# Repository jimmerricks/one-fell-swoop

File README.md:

# Swoop

A WIP fork of [David Barr's Sweep](https://github.com/davidphilipbarr/Sweep), which is itself based on the fabulous [Ferris by Pierre Chevalier](https://github.com/pierrechevalier83/ferris).

<span>

</span>

## Swoop MX / Howarya 🦞

| Front | Back |
| :---: | :---: |
|  |  |

### Features
⭕ Cherry MX style switches  
⭕ Hotswap support  
⭕ Per-key RGB LEDs (mini-e)  
⭕ Up to 2 encoders  
⭕ Oled screens  
⭕ Power switch for battery management  
⭕ Bluetooth support w/ nice!nano  
⭕ Plate style case with mcu cover

### Components list

To build and use a Swoop MX you will need:

* 1× PCB Kit
* 2× promicro compatible boards or 2 nice!nanos.
* 34-36× Cherry MX style switches
* 34-36× Kailh hotswap sockets
* 34-36× SK6812 Mini-E RGB SMD Leds (optional; not recommended for wireless)
* 34-36× keycaps
* 36× diodes (Surface-mount or Through-hole)
* 2× Rotary encoders & knobs (optional; ALPS EC11)
* 2× OLED LCD Display 128x32 SSD1306 (optional)
* 2× reset switches (optional; B3U-1000P(M))
* Some little rubber feet/bumpers
* 2× power switches (wireless only; MSK 12C02)
* 2× lipo batteries (wireless only; 301230 or 301228)
* 1× TRRS (not TRS!) cable (wired only)
* 2× TRRS Jack [PJ-320A] (wired only)
* 1× USB Cable (depends on your micro-controller choice)  

**For the case:**

* 32× M2 Screws (3mm thread length)  
* 10× M2 Standoff for the plates (7mm)
* 6× M2 Standoff for the controller cover (8mm)

### Price Estimate (5 keyboards)
* PCB - 10.13 USD
* Carbon fiber plate 1.6mm (base, switch, cover) - 37.09 USD
* Crylic plate 2.00mm (cover) - 6.42 USD
* nice!nanos - 41 USD
* Kailh Arctic Fox Switches - 66.86 USD
* Kailh hotswap sockets - 12.86 USD
* SK6812 Mini-E RGB SMD Leds - 10.00 USD
* keycaps - 92.00 USD
* diodes - 1.00 USD
* OLED LCD Display 128x32 SSD1306 - 10.00 USD
* reset switches B3U-1000P(M) - 1.00 USD
* power switches (wireless only; MSK 12C02) -- 0.68 USD
* lipo batteries (wireless only; 301230 or 301228) -- 8.2 USD
* TRRS (not TRS!) cable - 7.07 USD
* TRRS Jack [PJ-320A] - 0.86 USD
* USB Cable - 49.28 USD
* M2 Screw and Standoff - 5.00 USD

### How to build it

### Firmware

The firmware is available in QMK as `bluebell/swoop`.  
You can get started by using QMK's [online configurator](https://config.qmk.fm/#/bluebell/swoop/LAYOUT_split_3x5_3). Or check the [Swoop README file](https://github.com/qmk/qmk_firmware/blob/master/keyboards/bluebell/swoop/readme.md) to see how to compile the firmware locally.

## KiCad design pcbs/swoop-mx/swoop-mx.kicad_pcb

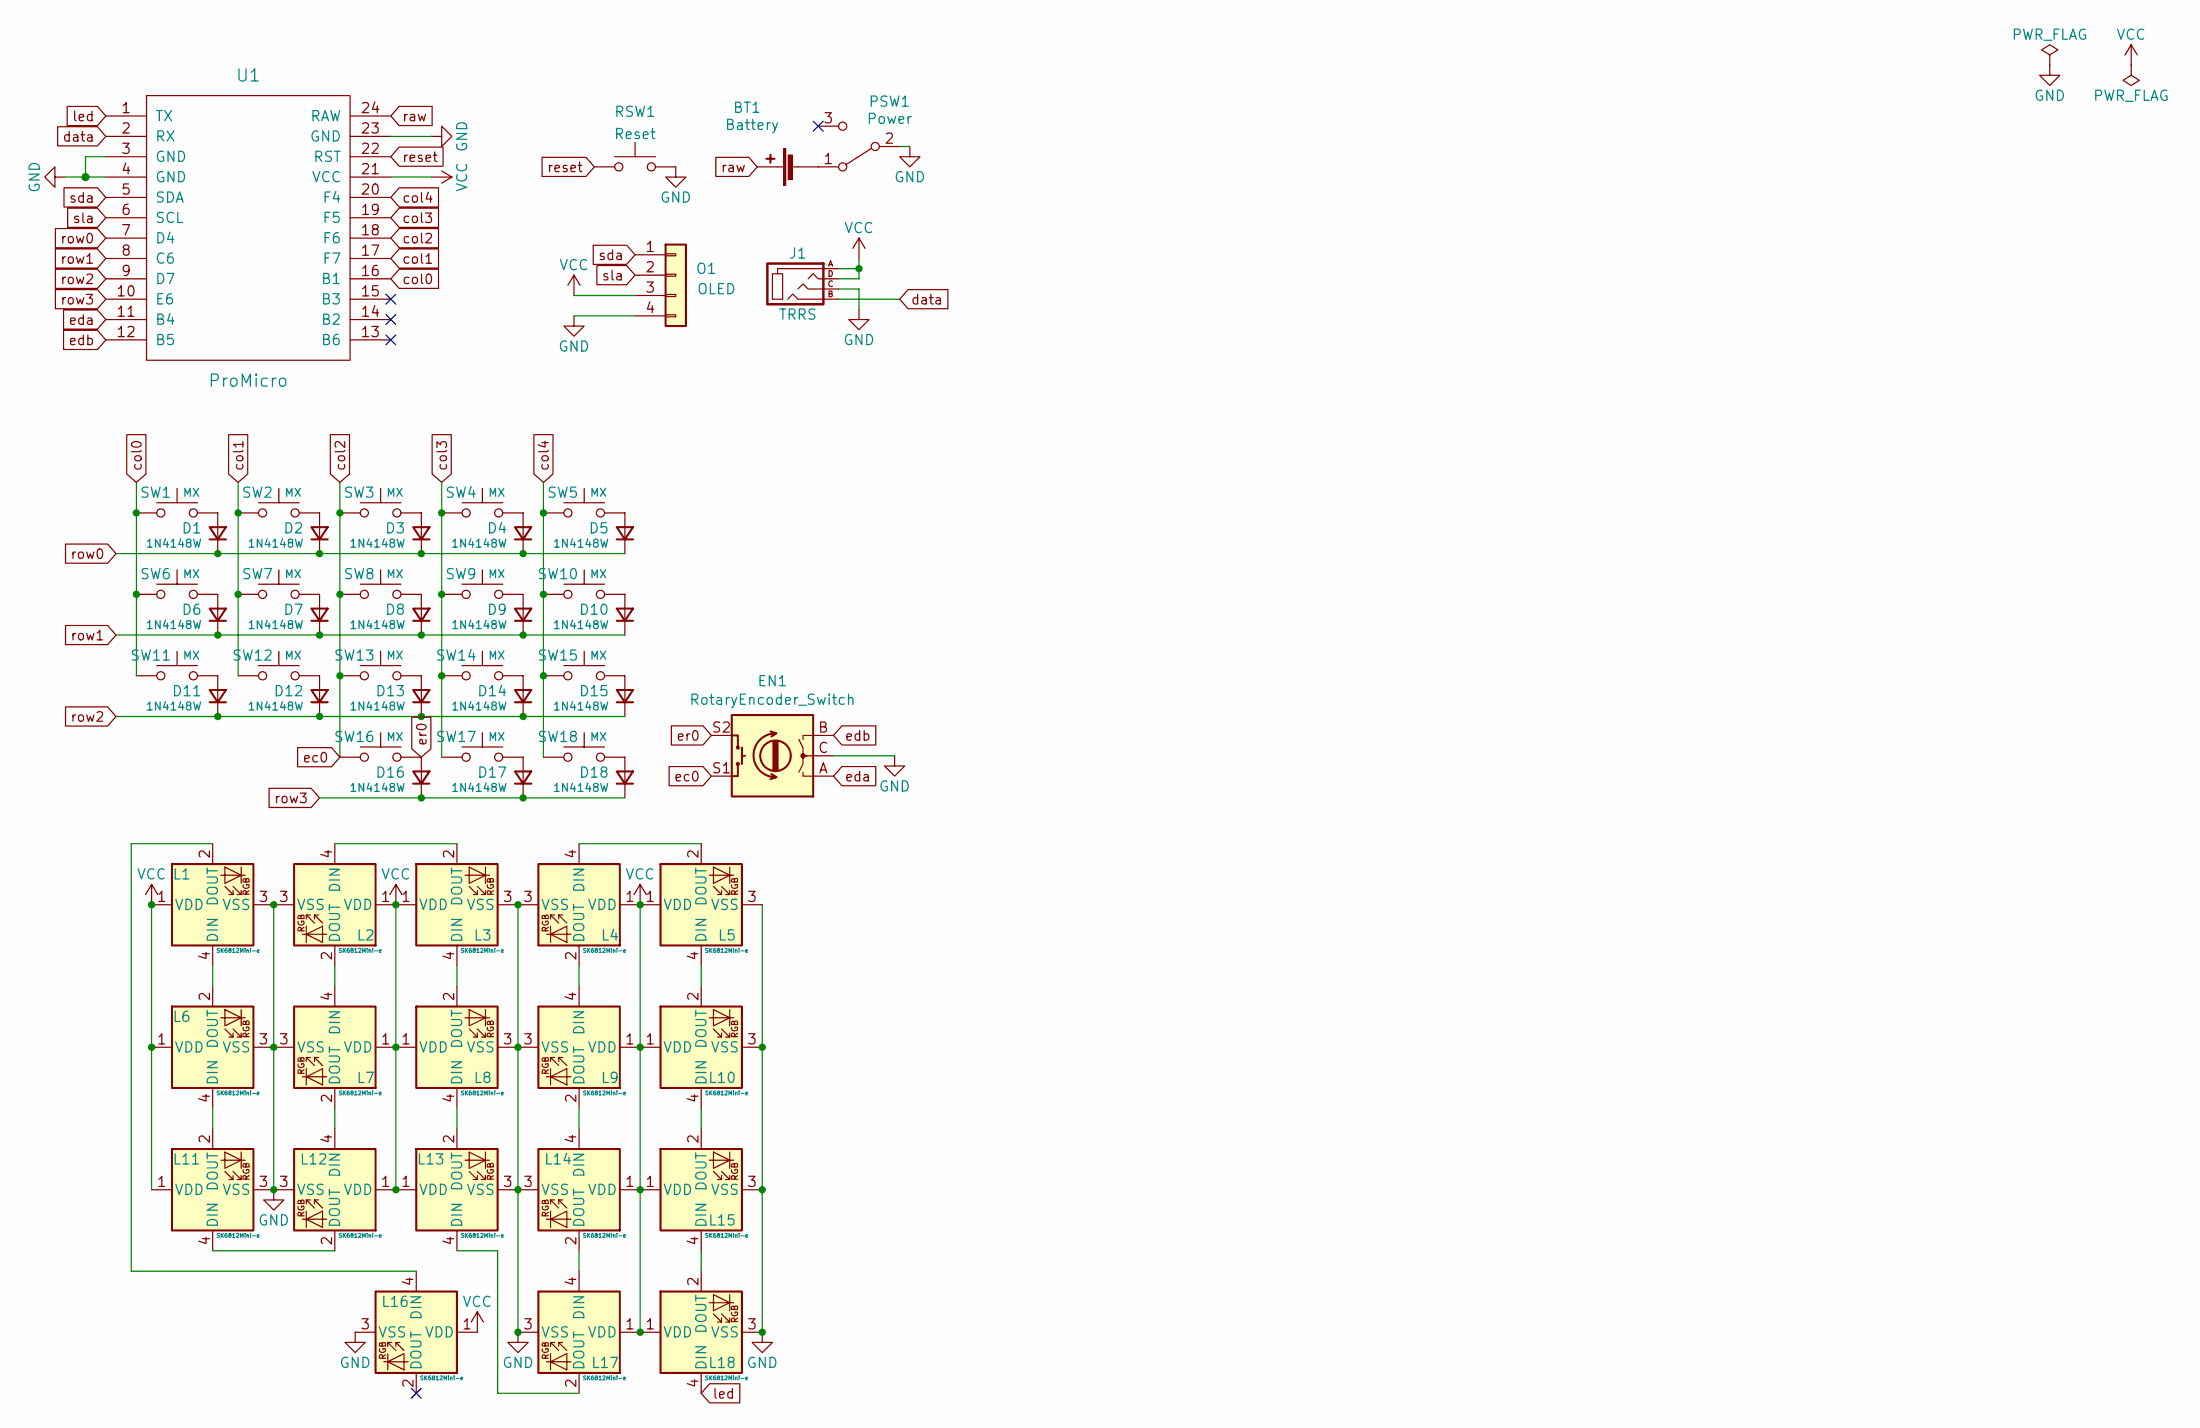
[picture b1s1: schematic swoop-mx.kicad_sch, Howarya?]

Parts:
BT1: Battery; Battery_pads_reversible
D1, D2, D3, D4, D5, D6, D7, D8, D9, D10, D11, D12, D13, D14, D15, D16, D17, D18: 1N4148W; D_SMD_TH
EN1: RotaryEncoder_Switch; RotaryEncoder
J1: TRRS; TRRS-3pin
L1, L2, L3, L4, L5, L6, L7, L8, L9, L10, L11, L12, L13, L14, L15, L16, L17, L18: SK6812Mini-e; SK6812_Mini_E; JLCPCB BOM 0
O1: OLED; OLED_jumpers
PSW1: Power
RSW1: Reset
SW1, SW2, SW3, SW4, SW5, SW6, SW7, SW8, SW9, SW10, SW11, SW12, SW13, SW14, SW15, SW16, SW17, SW18: MX; MX_socket_reversible
U1: ProMicro; ProMicro_jumpers

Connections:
GND: EN1.C, J1.C, L1.3 (VSS), L2.3 (VSS), L3.3 (VSS), L4.3 (VSS), L5.3 (VSS), L6.3 (VSS), L7.3 (VSS), L8.3 (VSS), L9.3 (VSS), L10.3 (VSS), L11.3 (VSS), L12.3 (VSS), L13.3 (VSS), L14.3 (VSS), L15.3 (VSS), L16.3 (VSS), L17.3 (VSS), L18.3 (VSS), O1.4, PSW1.2 (B), RSW1.2, U1.3 (GND), U1.4 (GND), U1.23 (GND)
unnamed: BT1.2 (-), PSW1.1 (A)
unnamed: D1.2 (A), SW1.2
unnamed: D2.2 (A), SW2.2
unnamed: D3.2 (A), SW3.2
unnamed: D4.2 (A), SW4.2
unnamed: D5.2 (A), SW5.2
unnamed: D6.2 (A), SW6.2
unnamed: D7.2 (A), SW7.2
unnamed: D8.2 (A), SW8.2
unnamed: D9.2 (A), SW9.2
unnamed: D10.2 (A), SW10.2
unnamed: D11.2 (A), SW11.2
unnamed: D12.2 (A), SW12.2
unnamed: D13.2 (A), SW13.2
unnamed: D14.2 (A), SW14.2
unnamed: D15.2 (A), SW15.2
unnamed: D17.2 (A), SW17.2
unnamed: D18.2 (A), SW18.2
unnamed: L1.2 (DOUT), L16.4 (DIN)
unnamed: L1.4 (DIN), L6.2 (DOUT)
unnamed: L2.2 (DOUT), L7.4 (DIN)
unnamed: L2.4 (DIN), L3.2 (DOUT)
unnamed: L3.4 (DIN), L8.2 (DOUT)
unnamed: L4.2 (DOUT), L9.4 (DIN)
unnamed: L4.4 (DIN), L5.2 (DOUT)
unnamed: L5.4 (DIN), L10.2 (DOUT)
unnamed: L6.4 (DIN), L11.2 (DOUT)
unnamed: L8.4 (DIN), L13.2 (DOUT)
unnamed: L10.4 (DIN), L15.2 (DOUT)
unnamed: L11.4 (DIN), L12.2 (DOUT)
unnamed: L7.2 (DOUT), L12.4 (DIN)
unnamed: L9.2 (DOUT), L14.4 (DIN)
unnamed: L13.4 (DIN), L17.2 (DOUT)
unnamed: L14.2 (DOUT), L17.4 (DIN)
unnamed: L15.4 (DIN), L18.2 (DOUT)
VCC: J1.A, J1.D, L1.1 (VDD), L2.1 (VDD), L3.1 (VDD), L4.1 (VDD), L5.1 (VDD), L6.1 (VDD), L7.1 (VDD), L8.1 (VDD), L9.1 (VDD), L10.1 (VDD), L11.1 (VDD), L12.1 (VDD), L13.1 (VDD), L14.1 (VDD), L15.1 (VDD), L16.1 (VDD), L17.1 (VDD), L18.1 (VDD), O1.3, U1.21 (VCC)
col0: SW1.1, SW6.1, SW11.1, U1.16 (B1)
col1: SW2.1, SW7.1, SW12.1, U1.17 (F7)
col2: EN1.S1, SW3.1, SW8.1, SW13.1, SW16.1, U1.18 (F6)
col3: SW4.1, SW9.1, SW14.1, SW17.1, U1.19 (F5)
col4: SW5.1, SW10.1, SW15.1, SW18.1, U1.20 (F4)
data: J1.B, U1.2 (RX)
eda: EN1.A, U1.11 (B4)
edb: EN1.B, U1.12 (B5)
er0: D16.2 (A), EN1.S2, SW16.2
led: L18.4 (DIN), U1.1 (TX)
raw: BT1.1 (+), U1.24 (RAW)
reset: RSW1.1, U1.22 (RST)
row0: D1.1 (K), D2.1 (K), D3.1 (K), D4.1 (K), D5.1 (K), U1.7 (D4)
row1: D6.1 (K), D7.1 (K), D8.1 (K), D9.1 (K), D10.1 (K), U1.8 (C6)
row2: D11.1 (K), D12.1 (K), D13.1 (K), D14.1 (K), D15.1 (K), U1.9 (D7)
row3: D16.1 (K), D17.1 (K), D18.1 (K), U1.10 (E6)
sda: O1.1, U1.5 (SDA)
sla: O1.2, U1.6 (SCL)

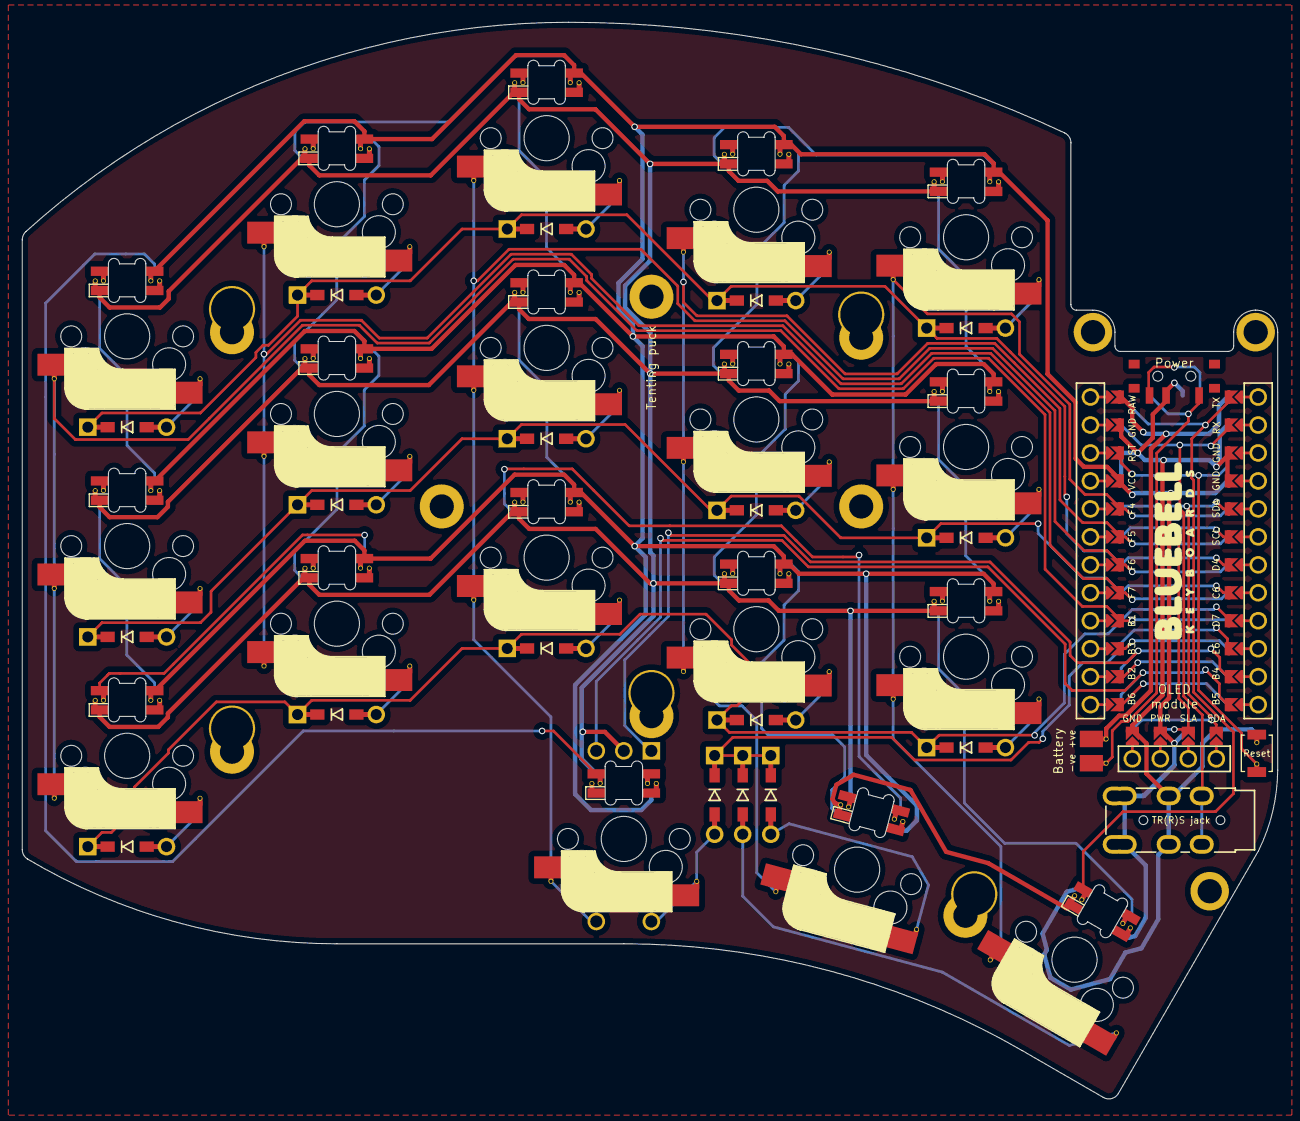
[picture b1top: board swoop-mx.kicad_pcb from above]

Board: 2 copper layers, 114.0 x 97.7 mm, 70 parts (0 on the bottom side), 55 nets.

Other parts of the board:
H1, H2, H3, H4, H4#2: M2 Hole; M2_double_hole_4mm
PUCK1: SYM_Arrow45_Small; Tenting_puck
Ref**: Val**; M2_hole_3.5mm
Ref**#2, Ref**#3: Val**; M2_hole_3.5mm

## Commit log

2022-09-10 Removed the Swoop Choc (for now) and updated the Swoop MX to 2.2
2022-09-10 Tidy up.
2022-09-10 Solid instead of hatch fill on plates.
2022-09-10 Rename file
2022-09-17 Add case hardware
2022-09-17 Fix gerber file extension
2022-11-09 update readme with diodes
2022-11-09 tht supported
    removed SMD from diodes, since tht appear to be supported.
2022-12-18 Add diode requirement, build guide, firmware
2023-01-15 Update screw count
2024-06-16 add plate dxf files
